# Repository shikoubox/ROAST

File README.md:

DTU Roadrunners Solar Team

Code and source files for all Solar Car parts and other related files. (e.g. PCBs, 3D prints, Embedded, Project materials, datasheets and literature)

# Structure
For parts, put all relevant for your part/project in a corresponding parts folder with, part and year.
For files that are larger than 100 MB, please upload them to OneDrive instead, and leave a link if relevant in this repository.

# CAD
All CAD is done in Solidworks.
Please provide technical drawings in .pdf, to avoid need for SolidWorks.

# Circuit Boards
All PCB design is done in KiCad.
There are old projects done in Eagle, but Autodesk has killed the Eagle.
Please provide schematics in .pdf, to avoid need for KiCad or Eagle, to see the circuit/board layout.

Also, both pdf, project, and silkscreen needs a tag with appropriate PCB title, date, revision no., and who made it (e.g. study number).

# Communication, discussion and questions
Please use the discord:
https://discord.gg/Wzs3dZkhpT

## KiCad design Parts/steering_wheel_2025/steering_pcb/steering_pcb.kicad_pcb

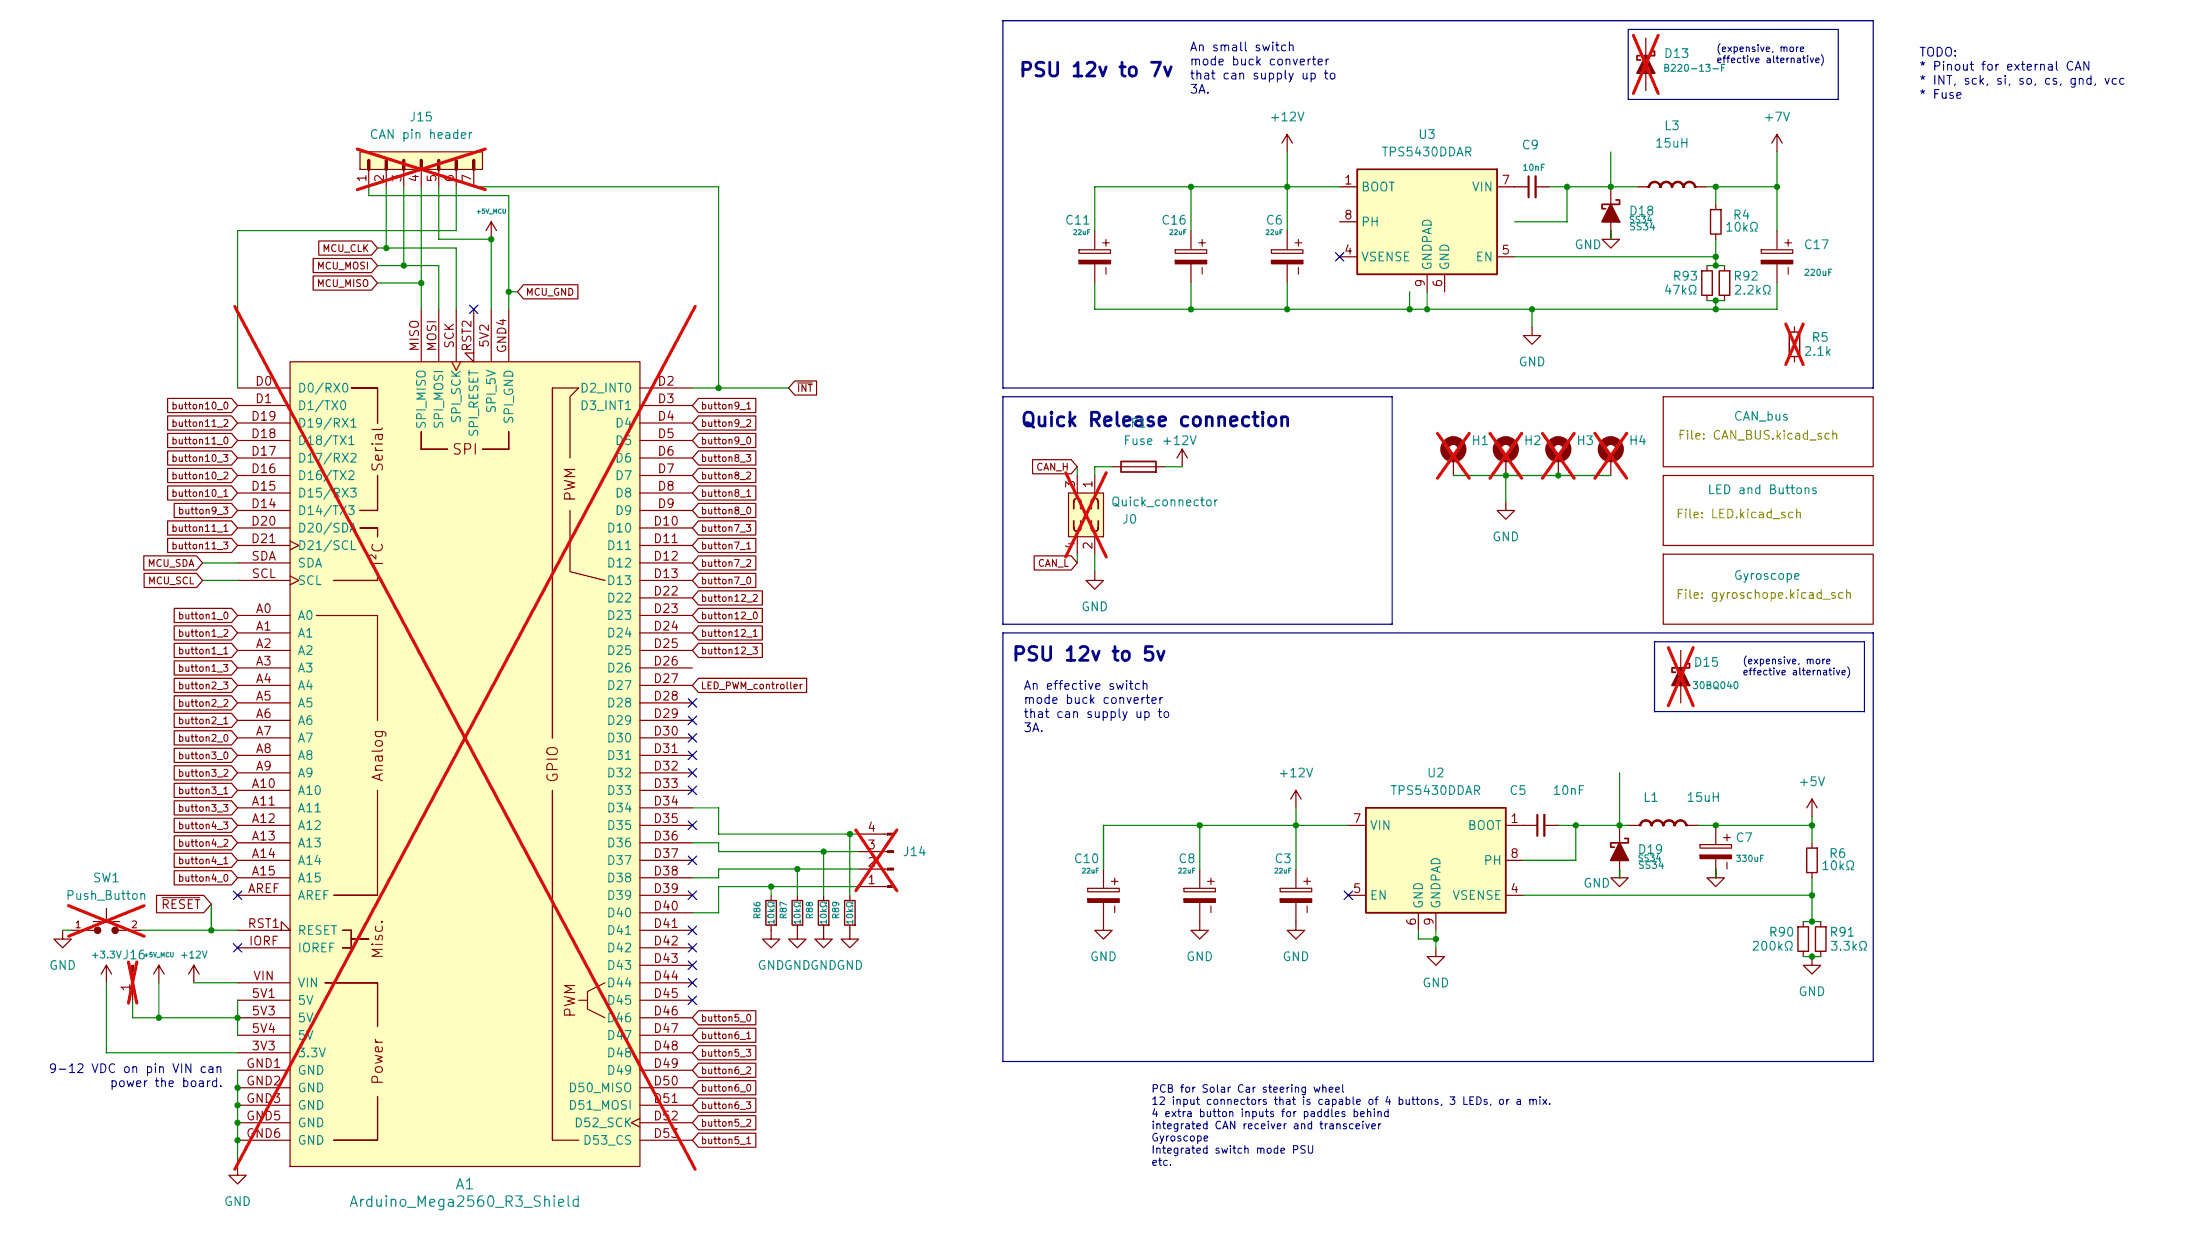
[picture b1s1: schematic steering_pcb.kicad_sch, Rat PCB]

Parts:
A1: Arduino_Mega2560_R3_Shield; not fitted
C3, C6, C8, C10, C11, C16: 22uF; C_1206_3216Metric_Pad1.33x1.80mm_HandSolder; JLCPCB C12891
C5, C9: 10nF; C_0402_1005Metric_Pad0.74x0.62mm_HandSolder; JLCPCB C1710
C7: 330uF; CP_EIA-7343-15_Kemet-W; JLCPCB C79112
C17: 220uF; CAP_10TPB220ML; JLCPCB C347545
D13: D_SMC; JLCPCB C110480; not fitted
D15: D_SMC; JLCPCB C468074; not fitted
D18, D19: SS34; D_SMA; JLCPCB C8678
F1: Fuse
H1, H2, H3, H4: MountingHole_Pad; MountingHole_2.2mm_M2_Pad; not fitted
J0: Quick_connector; Molex_Micro-Fit_3.0_43045-0412_2x02_P3.00mm_Vertical; JLCPCB C1329356; not fitted
J14: Conn_01x04_Pin; PinHeader_1x04_P2.54mm_Vertical; not fitted
J15: CAN pin header; PinHeader_1x07_P2.54mm_Vertical; not fitted
J16: Conn_01x01_Pin; PinSocket_1x01_P2.00mm_Vertical; not fitted
L1, L3: 15uH; L_Bourns_SRR1208_12.7x12.7mm; JLCPCB C1329356
R4, R6, R86, R87, R88, R89: 10kΩ; R_0402_1005Metric_Pad0.72x0.64mm_HandSolder; JLCPCB C25531
R5: 2.1k; R_0402_1005Metric_Pad0.72x0.64mm_HandSolder; JLCPCB C2998067; not fitted
R90: 200kΩ; R_0402_1005Metric_Pad0.72x0.64mm_HandSolder; Rating ±1%; JLCPCB C25764
R91: 3.3kΩ; R_0402_1005Metric_Pad0.72x0.64mm_HandSolder; JLCPCB C25890
R92: 2.2kΩ; R_0402_1005Metric_Pad0.72x0.64mm_HandSolder; JLCPCB C25879
R93: 47kΩ; R_0402_1005Metric_Pad0.72x0.64mm_HandSolder; JLCPCB C25792
SW1: Push_Button; SW_PUSH_6mm; JLCPCB C12368; not fitted
U2, U3: TPS5430DDAR; TI_SO-PowerPAD-8_ThermalVias; JLCPCB C9864

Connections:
+3.3V: A1.3V3 (3.3V); also elsewhere on the board
+5V: C7.1, L1.2 (-), R6.1; also elsewhere on the board
+5V_MCU: A1.5V1 (5V), A1.5V2 (SPI_5V), A1.5V3 (5V), A1.5V4 (5V), J15.5, J16.1; also elsewhere on the board
+7V: C17.1, L3.2 (-), R4.1; also elsewhere on the board
+12V: A1.VIN, C3.1, C6.1, C8.1, C10.1, C11.1, C16.1, F1.2, U2.7 (VIN), U3.1 (BOOT)
CAN_H: J0.3; also elsewhere on the board
CAN_L: J0.4; also elsewhere on the board
GND: A1.GND1 (GND), A1.GND2 (GND), A1.GND3 (GND), A1.GND5 (GND), A1.GND6 (GND), C3.2, C6.2, C7.2, C8.2, C10.2, C11.2, C16.2, C17.2, D18.2 (A), D19.2 (A), H1.1, H2.1, H3.1, H4.1, J0.2, R86.1, R87.1, R88.1, R89.1, R90.2, R91.2, R92.2, R93.2, SW1.1, U2.6 (GND), U2.9 (GNDPAD), U3.9 (GNDPAD); also elsewhere on the board
LED_PWM_controller: A1.D27; also elsewhere on the board
MCU_CLK: A1.SCK (SPI_SCK), J15.2; also elsewhere on the board
MCU_GND: A1.GND4 (SPI_GND), J15.1
MCU_MISO: A1.MISO (SPI_MISO), J15.4; also elsewhere on the board
MCU_MOSI: A1.MOSI (SPI_MOSI), J15.3; also elsewhere on the board
MCU_SCL: A1.SCL
MCU_SDA: A1.SDA
unnamed: A1.D0 (D0/RX0), J15.6
unnamed: C9.2, D18.1 (K), L3.1 (+)
unnamed: C5.2, D19.1 (K), L1.1 (+), U2.8 (PH)
unnamed: F1.1, J0.1
unnamed: A1.D40, J14.1, R86.2
unnamed: A1.D38, J14.2, R87.2
unnamed: A1.D36, J14.3, R88.2
unnamed: A1.D34, J14.4, R89.2
unnamed: C5.1, U2.1 (BOOT)
unnamed: R6.2, R90.1, R91.1, U2.4 (VSENSE)
unnamed: R4.2, R92.1, R93.1, U3.5 (EN)
unnamed: C9.1, U3.7 (VIN)
button1_0: A1.A0; also elsewhere on the board
button1_1: A1.A2; also elsewhere on the board
button1_2: A1.A1; also elsewhere on the board
button1_3: A1.A3; also elsewhere on the board
button2_0: A1.A7; also elsewhere on the board
button2_1: A1.A6; also elsewhere on the board
button2_2: A1.A5; also elsewhere on the board
button2_3: A1.A4; also elsewhere on the board
button3_0: A1.A8; also elsewhere on the board
button3_1: A1.A10; also elsewhere on the board
button3_2: A1.A9; also elsewhere on the board
button3_3: A1.A11; also elsewhere on the board
button4_0: A1.A15; also elsewhere on the board
button4_1: A1.A14; also elsewhere on the board
button4_2: A1.A13; also elsewhere on the board
button4_3: A1.A12; also elsewhere on the board
button5_0: A1.D46; also elsewhere on the board
button5_1: A1.D53 (D53_CS); also elsewhere on the board
button5_2: A1.D52 (D52_SCK); also elsewhere on the board
button5_3: A1.D48; also elsewhere on the board
button6_0: A1.D50 (D50_MISO); also elsewhere on the board
button6_1: A1.D47; also elsewhere on the board
button6_2: A1.D49; also elsewhere on the board
button6_3: A1.D51 (D51_MOSI); also elsewhere on the board
button7_0: A1.D13; also elsewhere on the board
button7_1: A1.D11; also elsewhere on the board
button7_2: A1.D12; also elsewhere on the board
button7_3: A1.D10; also elsewhere on the board
button8_0: A1.D9; also elsewhere on the board
button8_1: A1.D8; also elsewhere on the board
button8_2: A1.D7; also elsewhere on the board
button8_3: A1.D6; also elsewhere on the board
button9_0: A1.D5; also elsewhere on the board
button9_1: A1.D3 (D3_INT1); also elsewhere on the board
button9_2: A1.D4; also elsewhere on the board
button9_3: A1.D14 (D14/TX3); also elsewhere on the board
button10_0: A1.D1 (D1/TX0); also elsewhere on the board
button10_1: A1.D15 (D15/RX3); also elsewhere on the board
button10_2: A1.D16 (D16/TX2); also elsewhere on the board
button10_3: A1.D17 (D17/RX2); also elsewhere on the board
button11_0: A1.D18 (D18/TX1); also elsewhere on the board
button11_1: A1.D20 (D20/SDA); also elsewhere on the board
button11_2: A1.D19 (D19/RX1); also elsewhere on the board
button11_3: A1.D21 (D21/SCL); also elsewhere on the board
button12_0: A1.D23; also elsewhere on the board
button12_1: A1.D24; also elsewhere on the board
button12_2: A1.D22; also elsewhere on the board
button12_3: A1.D25; also elsewhere on the board
~INT: A1.D2 (D2_INT0), J15.7
~RESET: A1.RST1 (RESET), SW1.2; also elsewhere on the board

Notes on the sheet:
9-12 VDC on pin VIN can power the board.
PSU 12v to 7v
TODO: * Pinout for external CAN * INT, sck, si, so, cs, gnd, vcc * Fuse
(expensive, more effective alternative)
An small switch mode buck converter that can supply up to 3A.
PCB for Solar Car steering wheel 12 input connectors that is capable of 4 buttons, 3 LEDs, or a mix. 4 extra button inputs for paddles behind integrated CAN receiver and transceiver Gyroscope Integrated switch mode PSU etc.
An effective switch mode buck converter that can supply up to 3A.
Quick Release connection
PSU 12v to 5v

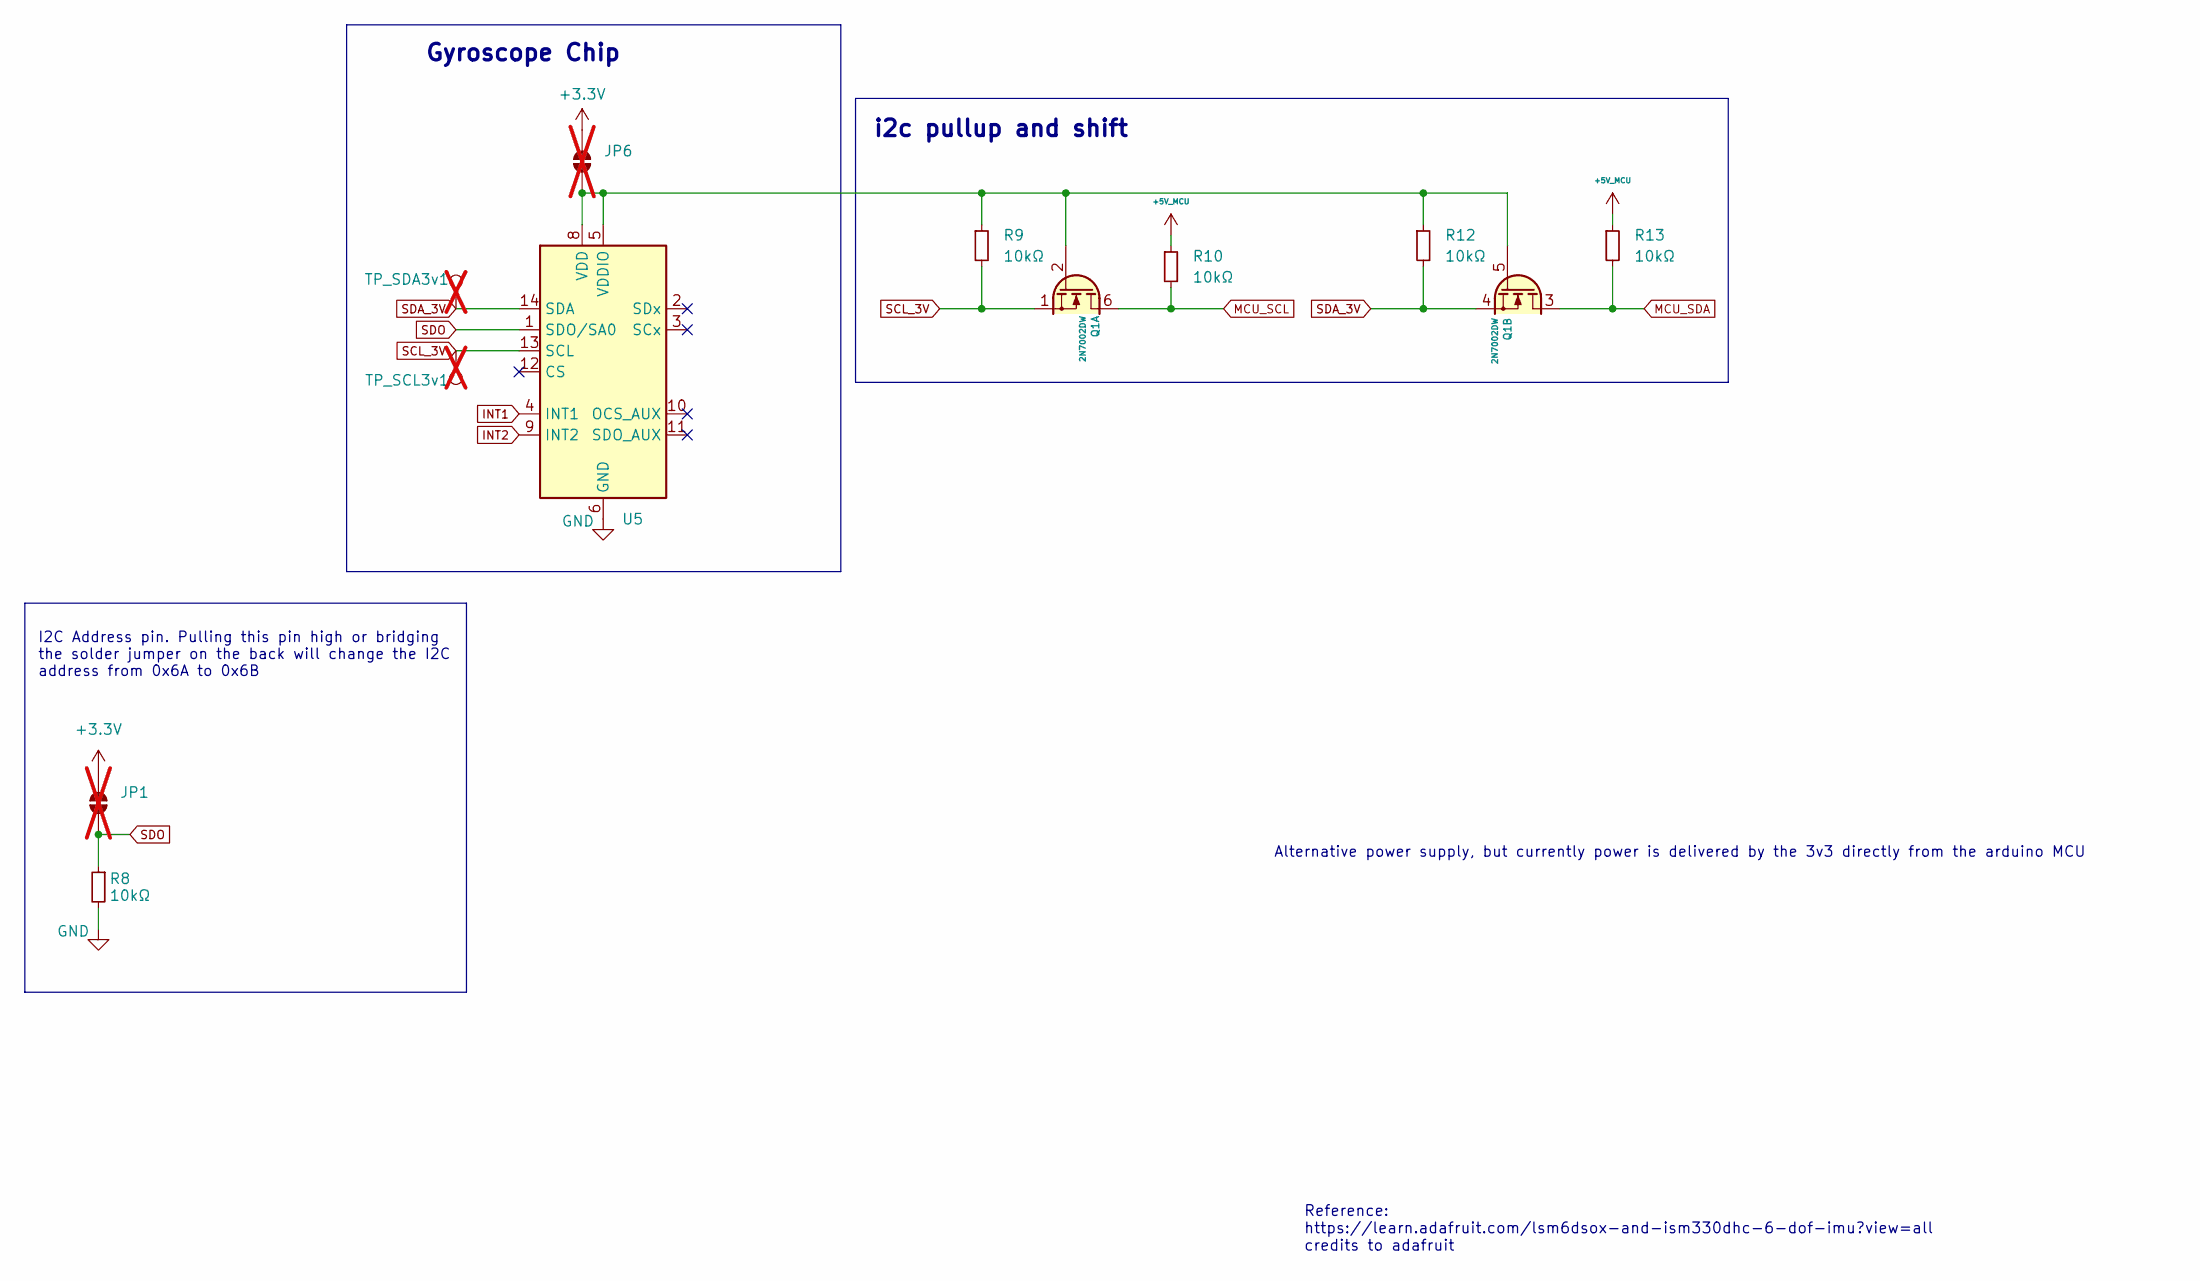
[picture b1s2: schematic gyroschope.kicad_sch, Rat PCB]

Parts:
JP1, JP6: SolderJumper-2_P1.3mm_Open_RoundedPad1.0x1.5mm; not fitted
Q1: 2N7002DW; SOT-363_SC-70-6; JLCPCB C2961242
R8, R9, R10, R12, R13: 10kΩ; R_0402_1005Metric_Pad0.72x0.64mm_HandSolder; JLCPCB C25531
TP_SCL3v1: SCL TestPoint; TestPoint_Pad_2.0x2.0mm; JLCPCB C9864; not fitted
TP_SDA3v1: 3v SDA TestPoint; TestPoint_Pad_2.0x2.0mm; JLCPCB C9864; not fitted
U5: LGA-14_3x2.5mm_P0.5mm_LayoutBorder3x4y; JLCPCB C2655101

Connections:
unnamed: JP1.1 (A), R8.1, U5.1 (SDO/SA0)
unnamed: JP1.2 (B), JP6.2 (B)
unnamed: JP6.1 (A), Q1.2 (G1), Q1.5 (G2), R9.1, R12.1, U5.5 (VDDIO), U5.8 (VDD)
unnamed: Q1.1 (S1), R9.2, TP_SCL3v1.1, U5.13 (SCL)
unnamed: Q1.3 (D2), R13.2
unnamed: Q1.4 (S2), R12.2, TP_SDA3v1.1, U5.14 (SDA)
unnamed: Q1.6 (D1), R10.2
unnamed: R8.2, U5.6 (GND), U5.7 (GND)
unnamed: R10.1, R13.1

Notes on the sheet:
Reference: https://learn.adafruit.com/lsm6dsox-and-ism330dhc-6-dof-imu?view=all credits to adafruit
Gyroscope Chip
Alternative power supply, but currently power is delivered by the 3v3 directly from the arduino MCU
I2C Address pin. Pulling this pin high or bridging the solder jumper on the back will change the I2C address from 0x6A to 0x6B
i2c pullup and shift

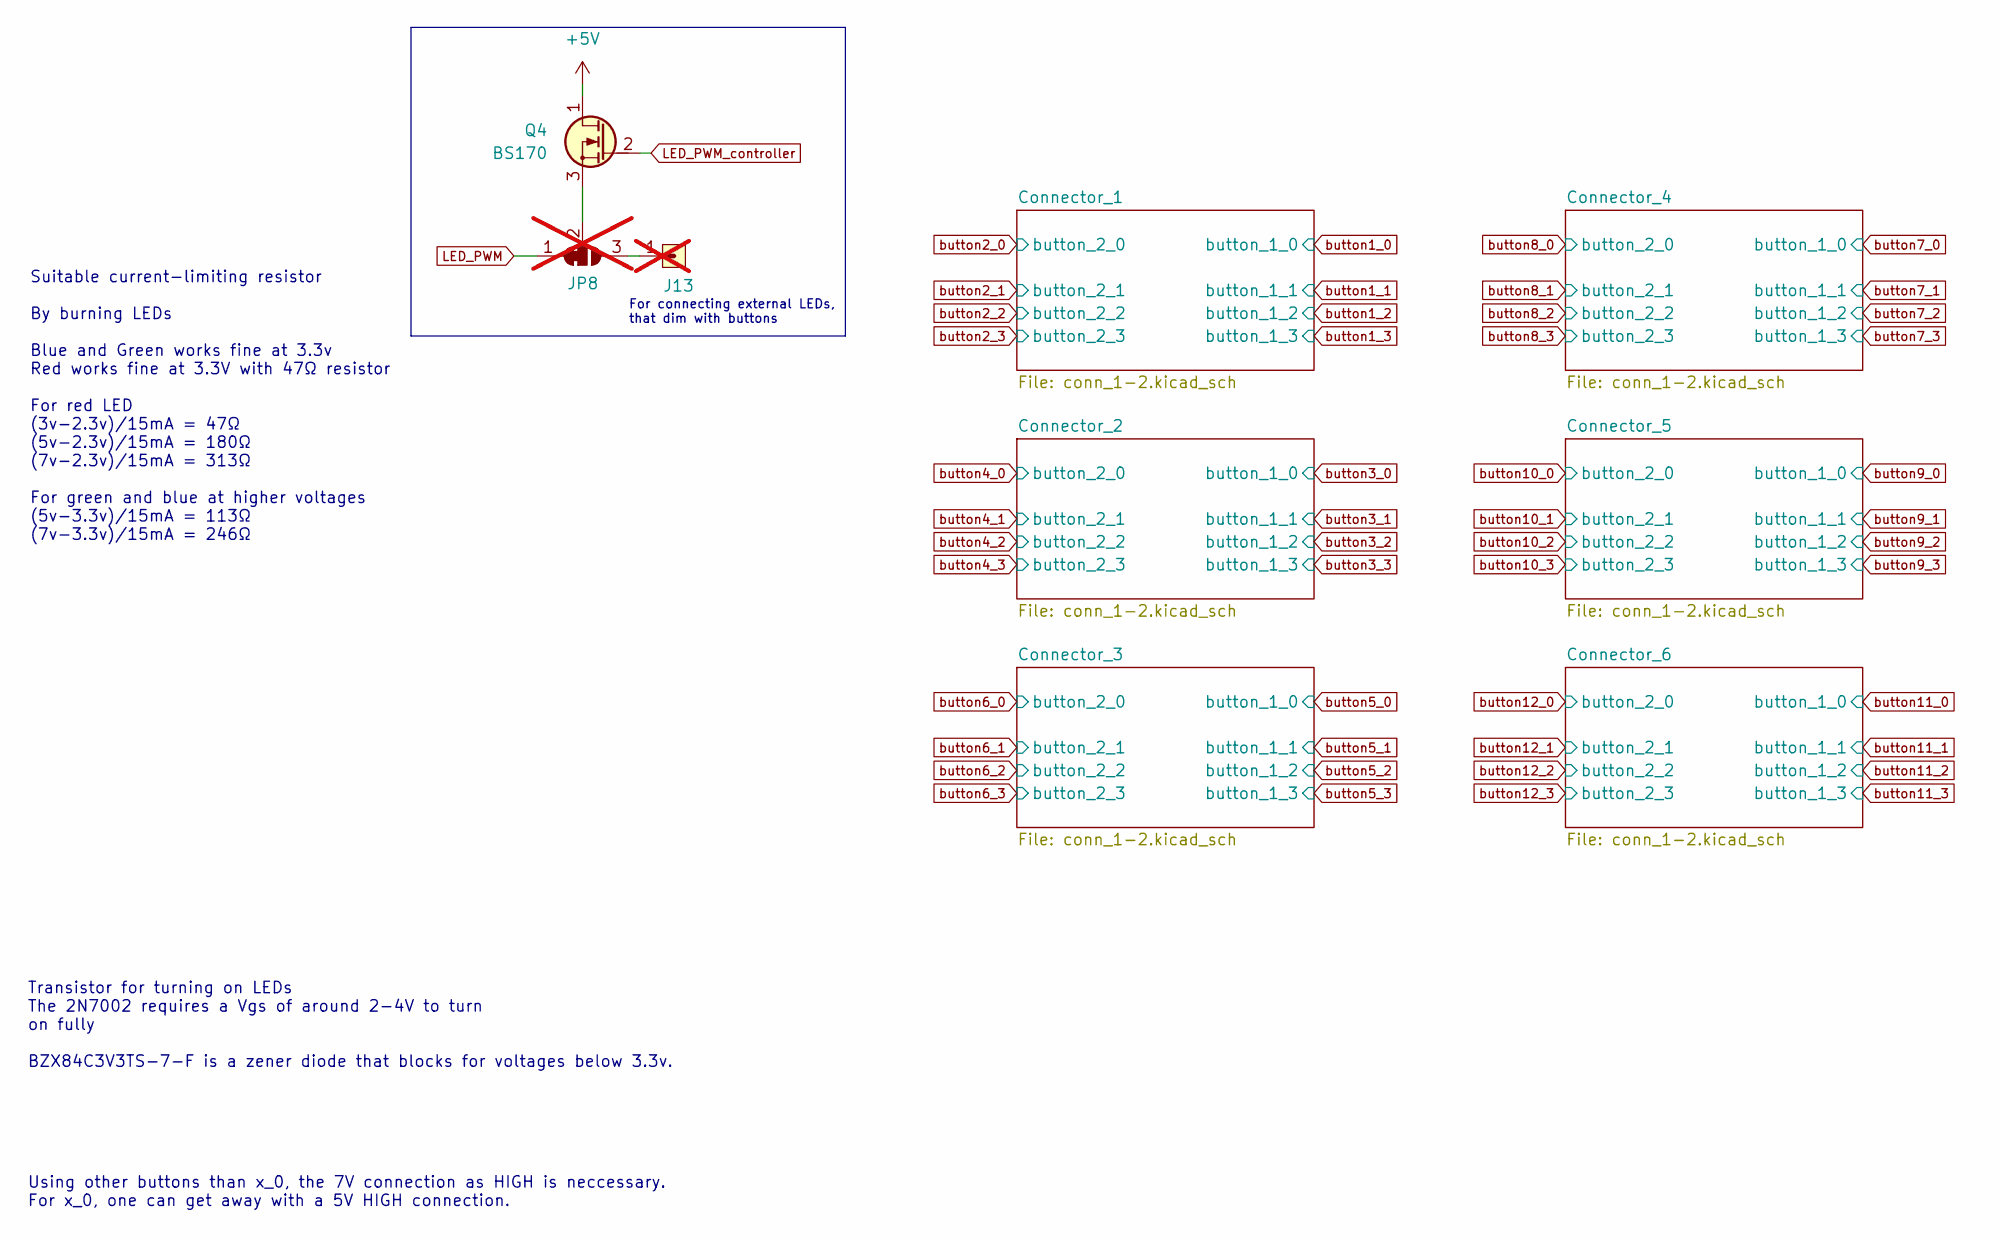
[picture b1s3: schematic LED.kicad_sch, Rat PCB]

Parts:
J13: PINHD_1x1_Male; PinHeader_1x01_P2.54mm_Vertical; JLCPCB C2961242; not fitted
JP8: SolderJumper-3_P1.3mm_Bridged12_RoundedPad1.0x1.5mm; not fitted
Q4: BS170; TO-92_Inline_Wide; JLCPCB C111691

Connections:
+5V: Q4.1 (D); also elsewhere on the board
LED_PWM: JP8.1 (A); also elsewhere on the board
LED_PWM_controller: Q4.2 (G); also elsewhere on the board
unnamed: J13.1, JP8.3 (B)
unnamed: JP8.2 (C), Q4.3 (S)

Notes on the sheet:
Transistor for turning on LEDs The 2N7002 requires a Vgs of around 2-4V to turn on fully BZX84C3V3TS-7-F is a zener diode that blocks for voltages below 3.3v.
Using other buttons than x_0, the 7V connection as HIGH is neccessary. For x_0, one can get away with a 5V HIGH connection.
For connecting external LEDs, that dim with buttons
Suitable current-limiting resistor By burning LEDs Blue and Green works fine at 3.3v Red works fine at 3.3V with 47Ω resistor For red LED (3v-2.3v)/15mA = 47Ω (5v-2.3v)/15mA = 180Ω (7v-2.3v)/15mA = 313Ω For green and blue at higher voltages (5v-3.3v)/15mA = 113Ω (7v-3.3v)/15mA = 246Ω

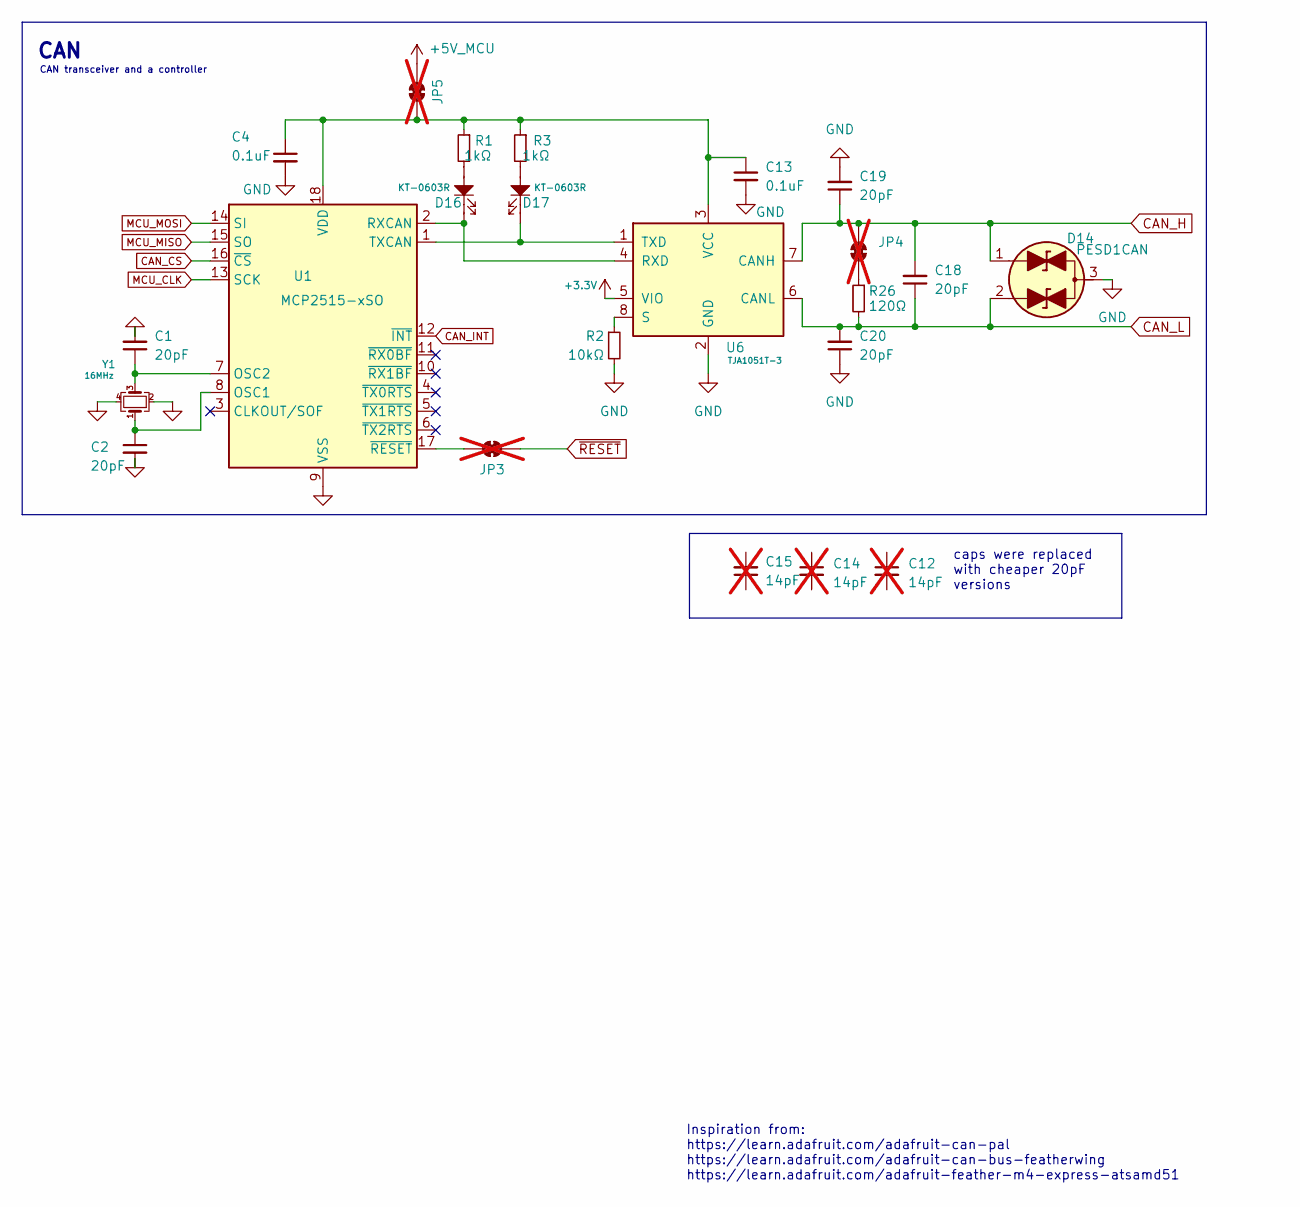
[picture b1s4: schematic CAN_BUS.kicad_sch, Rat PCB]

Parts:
C1, C2, C18, C19, C20: 20pF; C_0805_2012Metric_Pad1.18x1.45mm_HandSolder; JLCPCB C1798
C4, C13: 0.1uF; C_0805_2012Metric_Pad1.18x1.45mm_HandSolder; JLCPCB C49678
C12, C14, C15: 14pF; C_0805_2012Metric_Pad1.18x1.45mm_HandSolder; JLCPCB C63339; not fitted
D14: PESD1CAN; SOT-23; JLCPCB C907838
D16, D17: KT-0603R; LED_0603_1608Metric_Pad1.05x0.95mm_HandSolder; JLCPCB C2286
JP3, JP4, JP5: SolderJumper-2_P1.3mm_Bridged_RoundedPad1.0x1.5mm; not fitted
R1, R3: 1kΩ; R_0402_1005Metric_Pad0.72x0.64mm_HandSolder; JLCPCB C11702
R2: 10kΩ; R_0402_1005Metric_Pad0.72x0.64mm_HandSolder; JLCPCB C25531
R26: 120Ω; R_0402_1005Metric_Pad0.72x0.64mm_HandSolder; JLCPCB C25079
U1: MCP2515-xSO; SOIC-18W_7.5x11.6mm_P1.27mm; JLCPCB C12368
U6: TJA1051T-3; SOIC-8_3.9x4.9mm_P1.27mm; JLCPCB C5342108
Y1: 16MHz; Crystal_SMD_3225-4Pin_3.2x2.5mm; JLCPCB C13738

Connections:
+3.3V: U6.5 (VIO); also elsewhere on the board
+5V_MCU: JP5.2 (B); also elsewhere on the board
CAN_CS: U1.16 (~CS)
CAN_H: C18.2, C19.1, D14.1 (A1), JP4.2 (B), U6.7 (CANH); also elsewhere on the board
CAN_INT: U1.12 (~INT)
CAN_L: C18.1, C20.2, D14.2 (A2), R26.2, U6.6 (CANL); also elsewhere on the board
GND: C1.2, C2.2, C4.2, C13.2, C19.2, C20.1, D14.3 (Com), R2.2, U1.9 (VSS), U6.2 (GND), Y1.2, Y1.4; also elsewhere on the board
MCU_CLK: U1.13 (SCK); also elsewhere on the board
MCU_MISO: U1.15 (SO); also elsewhere on the board
MCU_MOSI: U1.14 (SI); also elsewhere on the board
unnamed: D16.2, R1.2
unnamed: D17.2, R3.2
unnamed: JP3.1 (A), U1.17 (~RESET)
unnamed: JP4.1 (A), R26.1
unnamed: C4.1, C13.1, JP5.1 (A), R1.1, R3.1, U1.18 (VDD), U6.3 (VCC)
unnamed: C2.1, U1.8 (OSC1), Y1.1
unnamed: C1.1, U1.7 (OSC2), Y1.3
unnamed: D16.1, U1.2 (RXCAN), U6.4 (RXD)
unnamed: D17.1, U1.1 (TXCAN), U6.1 (TXD)
unnamed: R2.1, U6.8 (S)
~RESET: JP3.2 (B); also elsewhere on the board

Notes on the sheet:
caps were replaced with cheaper 20pF versions
Inspiration from: https://learn.adafruit.com/adafruit-can-pal https://learn.adafruit.com/adafruit-can-bus-featherwing https://learn.adafruit.com/adafruit-feather-m4-express-atsamd51
CAN transceiver and a controller
CAN

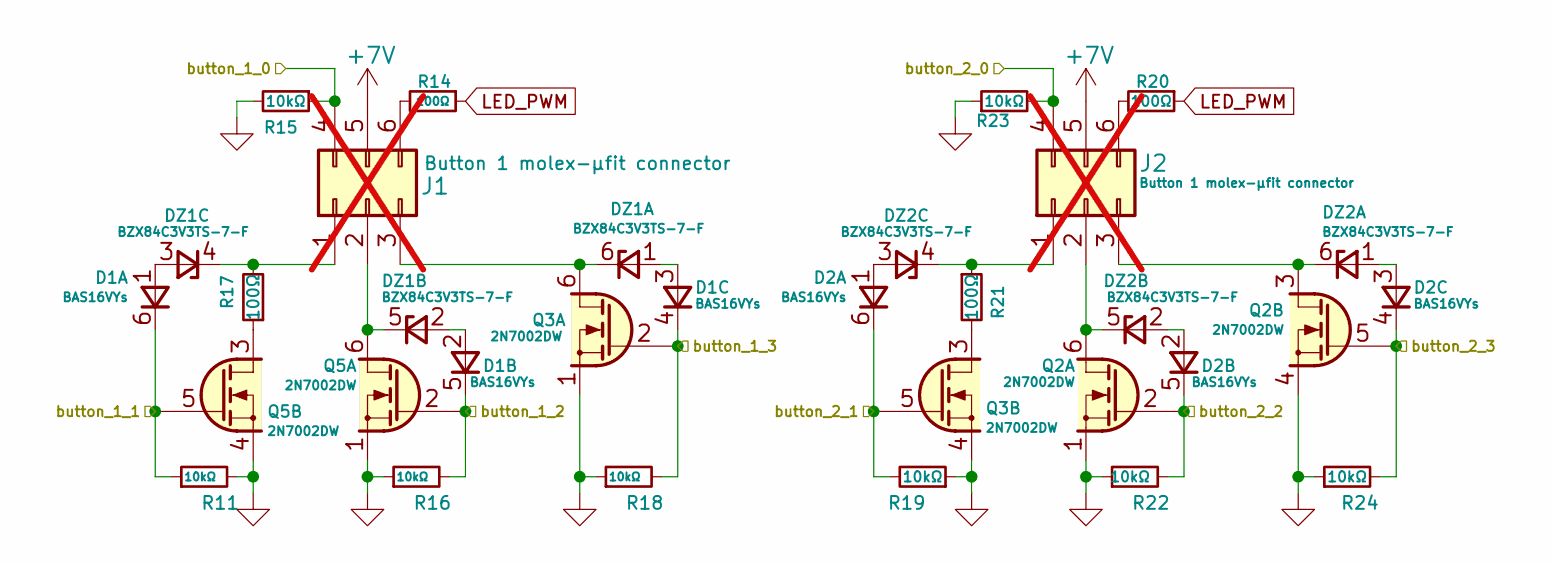
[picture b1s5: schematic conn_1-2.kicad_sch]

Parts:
D1, D2: BAS16VYs; SOT-363_SC-70-6; JLCPCB C135826
DZ1, DZ2: BZX84C3V3TS-7-F; SOT-363_SC-70-6; JLCPCB C5124989
J1, J2: Button 1 molex-µfit connector; Molex_Micro-Fit_3.0_43045-0612_2x03_P3.00mm_Vertical; not fitted
Q2, Q3, Q5: 2N7002DW; SOT-363_SC-70-6; JLCPCB C2961242
R11, R15, R16, R18, R19, R22, R23, R24: 10kΩ; R_0402_1005Metric_Pad0.72x0.64mm_HandSolder; JLCPCB C25531
R14, R17, R20, R21: 100Ω; R_0402_1005Metric_Pad0.72x0.64mm_HandSolder; JLCPCB C25076

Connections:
+7V: J1.5, J2.5; also elsewhere on the board
GND: Q2.1 (S1), Q2.4 (S2), Q3.1 (S1), Q3.4 (S2), Q5.1 (S1), Q5.4 (S2), R11.2, R15.2, R16.1, R18.1, R19.1, R22.1, R23.1, R24.1; also elsewhere on the board
LED_PWM: R14.1, R20.1; also elsewhere on the board
unnamed: D1.1 (A3), DZ1.3 (A3)
unnamed: D1.2 (A3), DZ1.2 (A2)
unnamed: D1.3 (A3), DZ1.1 (A1)
unnamed: D2.1 (A3), DZ2.3 (A3)
unnamed: D2.2 (A3), DZ2.2 (A2)
unnamed: D2.3 (A3), DZ2.1 (A1)
unnamed: DZ1.6 (C1), J1.3, Q3.6 (D1)
unnamed: DZ1.5 (C2), J1.2, Q5.6 (D1)
unnamed: DZ1.4 (C3), J1.1, R17.2
unnamed: DZ2.6 (C1), J2.3, Q2.3 (D2)
unnamed: DZ2.5 (C2), J2.2, Q2.6 (D1)
unnamed: DZ2.4 (C3), J2.1, R21.1
unnamed: J1.6, R14.2
unnamed: J2.6, R20.2
unnamed: Q3.3 (D2), R21.2
unnamed: Q5.3 (D2), R17.1
button1_0: J1.4, R15.1; also elsewhere on the board
button1_1: D1.6 (C3), Q5.5 (G2), R11.1; also elsewhere on the board
button1_2: D1.5 (C3), Q5.2 (G1), R16.2; also elsewhere on the board
button1_3: D1.4 (C3), Q3.2 (G1), R18.2; also elsewhere on the board
button2_0: J2.4, R23.2; also elsewhere on the board
button2_1: D2.6 (C3), Q3.5 (G2), R19.2; also elsewhere on the board
button2_2: D2.5 (C3), Q2.2 (G1), R22.2; also elsewhere on the board
button2_3: D2.4 (C3), Q2.5 (G2), R24.2; also elsewhere on the board

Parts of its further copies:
D3, D4, D5, D6, D7, D8, D9, D10, D11, D12: BAS16VYs; SOT-363_SC-70-6; JLCPCB C135826
DZ3, DZ4, DZ5, DZ6, DZ7, DZ8, DZ9, DZ10, DZ11, DZ12: BZX84C3V3TS-7-F; SOT-363_SC-70-6; JLCPCB C5124989
J3, J4, J5, J6, J7, J8, J9, J10, J11, J12: Button 1 molex-µfit connector; Molex_Micro-Fit_3.0_43045-0612_2x03_P3.00mm_Vertical; not fitted
Q7, Q8, Q9, Q10, Q11, Q12, Q13, Q14, Q15, Q16, Q17, Q18, Q19, Q20, Q21: 2N7002DW; SOT-363_SC-70-6; JLCPCB C2961242
R25, R28, R29, R31, R32, R35, R36, R37, R38, R40, R41, R43, R44, R47, R48, R49, R50, R52, R53, R55, R56, R59, R60, R61, R62, R64, R65, R67, R68, R71, R72, R73, R74, R76, R77, R79, R80, R83, R84, R85: 10kΩ; R_0402_1005Metric_Pad0.72x0.64mm_HandSolder; JLCPCB C25531
R27, R30, R33, R34, R39, R42, R45, R46, R51, R54, R57, R58, R63, R66, R69, R70, R75, R78, R81, R82: 100Ω; R_0402_1005Metric_Pad0.72x0.64mm_HandSolder; JLCPCB C25076

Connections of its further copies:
+7V: J3.5, J4.5, J5.5, J6.5, J7.5, J8.5, J9.5, J10.5, J11.5, J12.5; also elsewhere on the board
GND: Q7.1 (S1), Q7.4 (S2), Q8.1 (S1), Q8.4 (S2), Q9.1 (S1), Q9.4 (S2), Q10.1 (S1), Q10.4 (S2), Q11.1 (S1), Q11.4 (S2), Q12.1 (S1), Q12.4 (S2), Q13.1 (S1), Q13.4 (S2), Q14.1 (S1), Q14.4 (S2), Q15.1 (S1), Q15.4 (S2), Q16.1 (S1), Q16.4 (S2), Q17.1 (S1), Q17.4 (S2), Q18.1 (S1), Q18.4 (S2), Q19.1 (S1), Q19.4 (S2), Q20.1 (S1), Q20.4 (S2), Q21.1 (S1), Q21.4 (S2), R25.2, R28.2, R29.1, R31.1, R32.1, R35.1, R36.1, R37.1, R38.2, R40.2, R41.1, R43.1, R44.1, R47.1, R48.1, R49.1, R50.2, R52.2, R53.1, R55.1, R56.1, R59.1, R60.1, R61.1, R62.2, R64.2, R65.1, R67.1, R68.1, R71.1, R72.1, R73.1, R74.2, R76.2, R77.1, R79.1, R80.1, R83.1, R84.1, R85.1; also elsewhere on the board
LED_PWM: R30.1, R34.1, R42.1, R46.1, R54.1, R58.1, R66.1, R70.1, R78.1, R82.1; also elsewhere on the board
unnamed: D3.1 (A3), DZ3.3 (A3)
unnamed: D3.2 (A3), DZ3.2 (A2)
unnamed: D3.3 (A3), DZ3.1 (A1)
unnamed: D4.1 (A3), DZ4.3 (A3)
unnamed: D4.2 (A3), DZ4.2 (A2)
unnamed: D4.3 (A3), DZ4.1 (A1)
unnamed: D5.1 (A3), DZ5.3 (A3)
unnamed: D5.2 (A3), DZ5.2 (A2)
unnamed: D5.3 (A3), DZ5.1 (A1)
unnamed: D6.1 (A3), DZ6.3 (A3)
unnamed: D6.2 (A3), DZ6.2 (A2)
unnamed: D6.3 (A3), DZ6.1 (A1)
unnamed: D7.1 (A3), DZ7.3 (A3)
unnamed: D7.2 (A3), DZ7.2 (A2)
unnamed: D7.3 (A3), DZ7.1 (A1)
unnamed: D8.1 (A3), DZ8.3 (A3)
unnamed: D8.2 (A3), DZ8.2 (A2)
unnamed: D8.3 (A3), DZ8.1 (A1)
unnamed: D9.1 (A3), DZ9.3 (A3)
unnamed: D9.2 (A3), DZ9.2 (A2)
unnamed: D9.3 (A3), DZ9.1 (A1)
unnamed: D10.1 (A3), DZ10.3 (A3)
unnamed: D10.2 (A3), DZ10.2 (A2)
unnamed: D10.3 (A3), DZ10.1 (A1)
unnamed: D11.1 (A3), DZ11.3 (A3)
unnamed: D11.2 (A3), DZ11.2 (A2)
unnamed: D11.3 (A3), DZ11.1 (A1)
unnamed: D12.1 (A3), DZ12.3 (A3)
unnamed: D12.2 (A3), DZ12.2 (A2)
unnamed: D12.3 (A3), DZ12.1 (A1)
unnamed: DZ3.6 (C1), J3.3, Q8.6 (D1)
unnamed: DZ3.5 (C2), J3.2, Q7.6 (D1)
unnamed: DZ3.4 (C3), J3.1, R27.2
unnamed: DZ4.6 (C1), J4.3, Q9.3 (D2)
unnamed: DZ4.5 (C2), J4.2, Q9.6 (D1)
unnamed: DZ4.4 (C3), J4.1, R33.1
unnamed: DZ5.6 (C1), J5.3, Q11.6 (D1)
unnamed: DZ5.5 (C2), J5.2, Q10.6 (D1)
unnamed: DZ5.4 (C3), J5.1, R39.2
unnamed: DZ6.6 (C1), J6.3, Q12.3 (D2)
unnamed: DZ6.5 (C2), J6.2, Q12.6 (D1)
unnamed: DZ6.4 (C3), J6.1, R45.1
unnamed: DZ7.6 (C1), J7.3, Q14.6 (D1)
unnamed: DZ7.5 (C2), J7.2, Q13.6 (D1)
unnamed: DZ7.4 (C3), J7.1, R51.2
unnamed: DZ8.6 (C1), J8.3, Q15.3 (D2)
unnamed: DZ8.5 (C2), J8.2, Q15.6 (D1)
unnamed: DZ8.4 (C3), J8.1, R57.1
unnamed: DZ9.6 (C1), J9.3, Q17.6 (D1)
unnamed: DZ9.5 (C2), J9.2, Q16.6 (D1)
unnamed: DZ9.4 (C3), J9.1, R63.2
unnamed: DZ10.6 (C1), J10.3, Q18.3 (D2)
unnamed: DZ10.5 (C2), J10.2, Q18.6 (D1)
unnamed: DZ10.4 (C3), J10.1, R69.1
unnamed: DZ11.6 (C1), J11.3, Q20.6 (D1)
unnamed: DZ11.5 (C2), J11.2, Q19.6 (D1)
unnamed: DZ11.4 (C3), J11.1, R75.2
unnamed: DZ12.6 (C1), J12.3, Q21.3 (D2)
unnamed: DZ12.5 (C2), J12.2, Q21.6 (D1)
unnamed: DZ12.4 (C3), J12.1, R81.1
unnamed: J3.6, R30.2
unnamed: J4.6, R34.2
unnamed: J5.6, R42.2
unnamed: J6.6, R46.2
unnamed: J7.6, R54.2
unnamed: J8.6, R58.2
unnamed: J9.6, R66.2
unnamed: J10.6, R70.2
unnamed: J11.6, R78.2
unnamed: J12.6, R82.2
unnamed: Q7.3 (D2), R27.1
unnamed: Q8.3 (D2), R33.2
unnamed: Q10.3 (D2), R39.1
unnamed: Q11.3 (D2), R45.2
unnamed: Q13.3 (D2), R51.1
unnamed: Q14.3 (D2), R57.2
unnamed: Q16.3 (D2), R63.1
unnamed: Q17.3 (D2), R69.2
unnamed: Q19.3 (D2), R75.1
unnamed: Q20.3 (D2), R81.2
button3_0: J3.4, R28.1; also elsewhere on the board
button3_1: D3.6 (C3), Q7.5 (G2), R25.1; also elsewhere on the board
button3_2: D3.5 (C3), Q7.2 (G1), R29.2; also elsewhere on the board
button3_3: D3.4 (C3), Q8.2 (G1), R31.2; also elsewhere on the board
button4_0: J4.4, R36.2; also elsewhere on the board
button4_1: D4.6 (C3), Q8.5 (G2), R32.2; also elsewhere on the board
button4_2: D4.5 (C3), Q9.2 (G1), R35.2; also elsewhere on the board
button4_3: D4.4 (C3), Q9.5 (G2), R37.2; also elsewhere on the board
button5_0: J5.4, R40.1; also elsewhere on the board
button5_1: D5.6 (C3), Q10.5 (G2), R38.1; also elsewhere on the board
button5_2: D5.5 (C3), Q10.2 (G1), R41.2; also elsewhere on the board
button5_3: D5.4 (C3), Q11.2 (G1), R43.2; also elsewhere on the board
button6_0: J6.4, R48.2; also elsewhere on the board
button6_1: D6.6 (C3), Q11.5 (G2), R44.2; also elsewhere on the board
button6_2: D6.5 (C3), Q12.2 (G1), R47.2; also elsewhere on the board
button6_3: D6.4 (C3), Q12.5 (G2), R49.2; also elsewhere on the board
button7_0: J7.4, R52.1; also elsewhere on the board
button7_1: D7.6 (C3), Q13.5 (G2), R50.1; also elsewhere on the board
button7_2: D7.5 (C3), Q13.2 (G1), R53.2; also elsewhere on the board
button7_3: D7.4 (C3), Q14.2 (G1), R55.2; also elsewhere on the board
button8_0: J8.4, R60.2; also elsewhere on the board
button8_1: D8.6 (C3), Q14.5 (G2), R56.2; also elsewhere on the board
button8_2: D8.5 (C3), Q15.2 (G1), R59.2; also elsewhere on the board
button8_3: D8.4 (C3), Q15.5 (G2), R61.2; also elsewhere on the board
button9_0: J9.4, R64.1; also elsewhere on the board
button9_1: D9.6 (C3), Q16.5 (G2), R62.1; also elsewhere on the board
button9_2: D9.5 (C3), Q16.2 (G1), R65.2; also elsewhere on the board
button9_3: D9.4 (C3), Q17.2 (G1), R67.2; also elsewhere on the board
button10_0: J10.4, R72.2; also elsewhere on the board
button10_1: D10.6 (C3), Q17.5 (G2), R68.2; also elsewhere on the board
button10_2: D10.5 (C3), Q18.2 (G1), R71.2; also elsewhere on the board
button10_3: D10.4 (C3), Q18.5 (G2), R73.2; also elsewhere on the board
button11_0: J11.4, R76.1; also elsewhere on the board
button11_1: D11.6 (C3), Q19.5 (G2), R74.1; also elsewhere on the board
button11_2: D11.5 (C3), Q19.2 (G1), R77.2; also elsewhere on the board
button11_3: D11.4 (C3), Q20.2 (G1), R79.2; also elsewhere on the board
button12_0: J12.4, R84.2; also elsewhere on the board
button12_1: D12.6 (C3), Q20.5 (G2), R80.2; also elsewhere on the board
button12_2: D12.5 (C3), Q21.2 (G1), R83.2; also elsewhere on the board
button12_3: D12.4 (C3), Q21.5 (G2), R85.2; also elsewhere on the board
